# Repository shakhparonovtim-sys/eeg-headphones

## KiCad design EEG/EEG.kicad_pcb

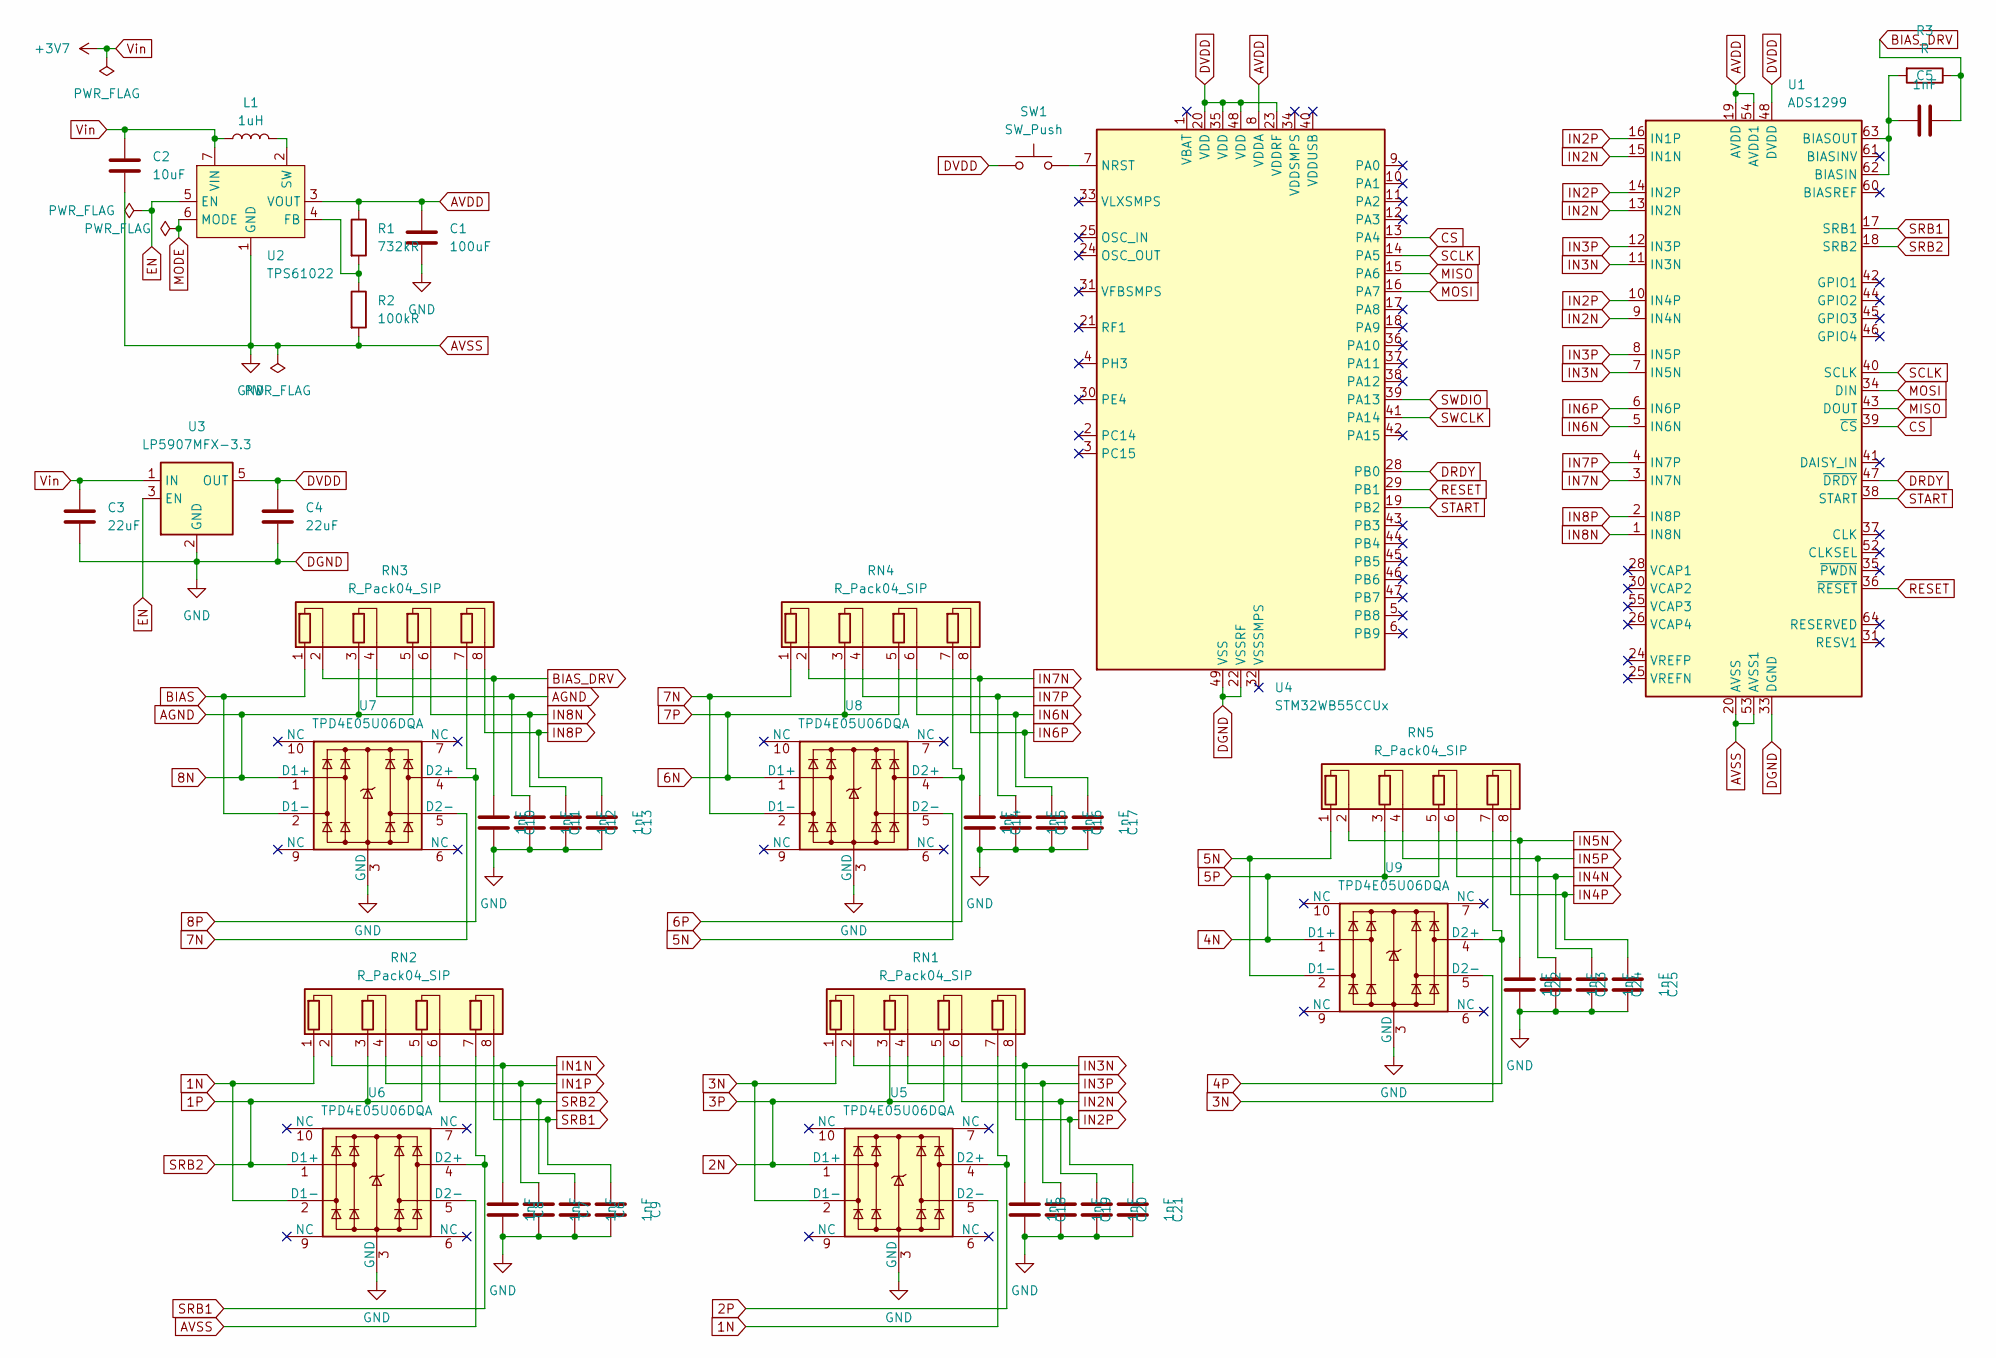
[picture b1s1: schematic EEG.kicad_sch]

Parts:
C1: 100uF; CP_Elec_3x5.3
C2: 10uF; CP_Elec_3x5.3
C3, C4: 22uF; CP_Elec_3x5.3
C5, C6, C7, C8, C9, C10, C11, C12, C13, C14, C15, C16, C17, C18, C19, C20, C21, C22, C23, C24, C25: 1nF; CP_Elec_3x5.3
L1: 1uH; L_6.3x6.3_H3
R1: 732kR; R_0201_0603Metric
R2: 100kR; R_0201_0603Metric
R3: R; R_0201_0603Metric
RN1, RN2, RN3, RN4, RN5: R_Pack04_SIP; R_Array_SIP8
SW1: SW_Push; SW_DIP_SPSTx02_Slide_Omron_A6S-210x_W8.9mm_P2.54mm
U1: ADS1299; TQFP-64_10x10mm_P0.5mm
U2: TPS61022; Texas_RWU0007A_VQFN-7_2x2mm_P0.5mm
U3: LP5907MFX-3.3; SOT-23-5
U4: STM32WB55CCUx; QFN-48-1EP_7x7mm_P0.5mm_EP5.6x5.6mm
U5, U6, U7, U8, U9: TPD4E05U06DQA; USON-10_2.5x1.0mm_P0.5mm

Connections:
1N: RN2.1 (R1.1), U5.5 (D2-), U6.2 (D1-)
1P: C6.2, RN2.3 (R2.1), RN2.5 (R3.1), RN2.6 (R3.2), U1.18 (SRB2), U6.1 (D1+)
2N: RN1.3 (R2.1), RN1.5 (R3.1), U5.1 (D1+)
2P: RN1.7 (R4.1), U5.4 (D2+)
3N: RN1.1 (R1.1), U5.2 (D1-), U9.5 (D2-)
4N: RN5.3 (R2.1), RN5.5 (R3.1), U9.1 (D1+)
4P: RN5.7 (R4.1), U9.4 (D2+)
5N: RN5.1 (R1.1), U8.5 (D2-), U9.2 (D1-)
6N: RN4.3 (R2.1), RN4.5 (R3.1), U8.1 (D1+)
6P: RN4.7 (R4.1), U8.4 (D2+)
7N: RN4.1 (R1.1), U7.5 (D2-), U8.2 (D1-)
8N: C11.2, RN3.3 (R2.1), RN3.4 (R2.2), RN3.5 (R3.1), U7.1 (D1+)
8P: RN3.7 (R4.1), U7.4 (D2+)
AVDD: C1.1, R1.1, U1.19 (AVDD), U1.21 (AVDD), U1.22 (AVDD), U1.54 (AVDD1), U1.56 (AVDD), U1.59 (AVDD), U2.3 (VOUT), U4.8 (VDDA)
AVSS: C1.2, C2.2, C3.2, C4.2, C6.1, C7.1, C8.1, C9.1, C10.1, C11.1, C12.1, C13.1, C14.1, C15.1, C16.1, C17.1, C18.1, C19.1, C20.1, C21.1, C22.1, C23.1, C24.1, C25.1, R2.2, U1.20 (AVSS), U1.23 (AVSS), U1.32 (AVSS), U1.33 (DGND), U1.49 (DGND), U1.51 (DGND), U1.53 (AVSS1), U1.57 (AVSS), U1.58 (AVSS), U2.1 (GND), U3.2 (GND), U4.22 (VSSRF), U4.49 (VSS), U5.3 (GND), U5.8 (GND), U6.3 (GND), U6.5 (D2-), U6.8 (GND), U7.3 (GND), U7.8 (GND), U8.3 (GND), U8.8 (GND), U9.3 (GND), U9.8 (GND)
BIAS: RN3.1 (R1.1), U7.2 (D1-)
BIAS_DRV: C5.1, C10.2, R3.1, RN3.2 (R1.2)
CS: U1.39 (~CS), U4.13 (PA4)
DRDY: U1.47 (~DRDY), U4.28 (PB0)
DVDD: C4.1, SW1.1, U1.48 (DVDD), U1.50 (DVDD), U3.5 (OUT), U4.20 (VDD), U4.23 (VDDRF), U4.35 (VDD), U4.48 (VDD)
EN: U2.5 (EN), U3.3 (EN)
IN1N: C8.2, RN2.2 (R1.2)
IN1P: C7.2, RN2.4 (R2.2)
IN2N: C20.2, RN1.6 (R3.2), U1.9 (IN4N), U1.13 (IN2N), U1.15 (IN1N)
IN2P: C21.2, RN1.8 (R4.2), U1.10 (IN4P), U1.14 (IN2P), U1.16 (IN1P)
IN3N: C18.2, RN1.2 (R1.2), U1.7 (IN5N), U1.11 (IN3N)
IN3P: C19.2, RN1.4 (R2.2), U1.8 (IN5P), U1.12 (IN3P)
IN4N: C24.2, RN5.6 (R3.2)
IN4P: C25.2, RN5.8 (R4.2)
IN5N: C22.2, RN5.2 (R1.2)
IN5P: C23.2, RN5.4 (R2.2)
IN6N: C16.2, RN4.6 (R3.2), U1.5 (IN6N)
IN6P: C17.2, RN4.8 (R4.2), U1.6 (IN6P)
IN7N: C14.2, RN4.2 (R1.2), U1.3 (IN7N)
IN7P: C15.2, RN4.4 (R2.2), U1.4 (IN7P)
IN8N: C12.2, RN3.6 (R3.2), U1.1 (IN8N)
IN8P: C13.2, RN3.8 (R4.2), U1.2 (IN8P)
MISO: U1.43 (DOUT), U4.15 (PA6)
MODE: U2.6 (MODE)
MOSI: U1.34 (DIN), U4.16 (PA7)
unnamed: C5.2, R3.2, U1.62 (BIASIN), U1.63 (BIASOUT)
unnamed: R1.2, R2.1, U2.4 (FB)
unnamed: L1.2, U2.2 (SW)
unnamed: SW1.2, U4.7 (NRST)
RESET: U1.36 (~RESET), U4.29 (PB1)
SCLK: U1.40 (SCLK), U4.14 (PA5)
SRB1: C9.2, RN2.7 (R4.1), RN2.8 (R4.2), U1.17 (SRB1), U6.4 (D2+)
START: U1.38 (START), U4.19 (PB2)
SWCLK: U4.41 (PA14)
SWDIO: U4.39 (PA13)
Vin: C2.1, C3.1, L1.1, U2.7 (VIN), U3.1 (IN)

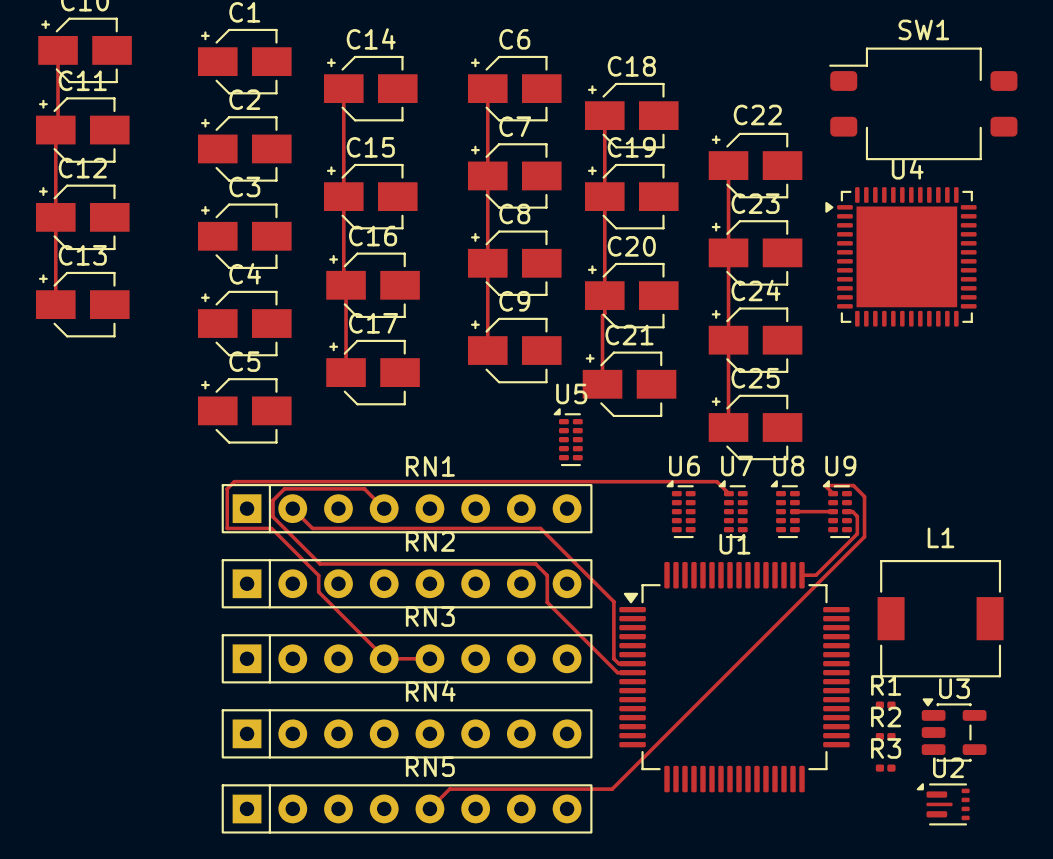
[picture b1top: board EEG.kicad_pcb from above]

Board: 2 copper layers, 44 parts (0 on the bottom side), 48 nets.
